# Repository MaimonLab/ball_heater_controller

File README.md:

# Ball Heater Controller

This repo contains the schematics and associated code for a controller to control the temperature of a ball holder or other device using closed loop PID drive of a resistive heater. There is a Python class to interact with the controller over USB-Serial, as well as a ROS2 Node to send and receive commands with the controller using ROS2.

For instructions on building a Ball Heater Controller, see [Assembly.](docs/assembly.md)

## Basic Usage

The Ball Heater Controller can be used independently of a computer by simply supplying it with AC power and attaching a ball heater and thermistor assembly to the main 4 pin output port on the front.

You can then change the mode by pressing and holding the control knob (see [Modes](#controller-modes)), and set the temperature setpoint (shown lower left as `SP:` on the LCD) by turning the knob. Current temperature is shown bottom right on the LCD.

### Python

The device can also be used with a computer for greater control and temperature logging. Interaction is done over USB-Serial, and the computer side is managed through the `BallHeaterDriver` Python class found in [`ball_heater_driver.py`](ball_heater_controller/ball_heater_controller/ball_heater_driver.py). An example of how this class can be used can be found in the Jupyter Notebook [`ball_heater_controller_testing.ipynb`](ball_heater_controller/ball_heater_controller/ball_heater_controller_testing.ipynb)

In short, after creating a `BallHeaterDriver` object, providing the correct serial port, commands can be sent using the `send_command` method. The main commands you will use are `status`, `set_target_temp`, and `set_control_mode`. Valid syntax for creating an object and sending these commands is shown below, with the first valid serial port chosen by default.

```python
import ball_heater_driver 
from list_ports import list_ports
import time

ports = [
    port
    for port in list_ports()
    if port["manufacturer"] is not None and "Silicon Labs" in port["manufacturer"]
]
port = ports[0]["port"]
print(f"Using Port: {port}")
ball_heater = ball_heater_driver.BallHeaterDriver(port=port)

# wait for the device to reset
time.sleep(5)

# Get and print status
success, status = ball_heater.send_command('status', [])
print('current status is:')
print('\n'.join((f"{key} : {value}") for key, value in status.items()))

# Set the target temperature to 35 (will also set control mode to remote)
ball_heater.send_command("set_target_temp", [35])

# Set the control mode back to standby
ball_heater.send_command("set_control_mode", ["standby"])
```

### ROS2

There is also a ROS2 Node provided for interacting with the Ball Heater Controller, [`ball_heater_node.py`](ball_heater_controller/ball_heater_controller/ball_heater_node.py).  The launch file [example_ball_heater.launch.py](ball_heater_controller/launch/example_ball_heater.launch.py), along with the config file [example_config.yaml](ball_heater_controller/config/example_config.yaml) will launch the node, as well as an example client node that can interact with the ball_heater_node.  It will also launch the ball_heater_gui that will subscribe to and print the heater status, and let the user set the temperature setpoint.  Once installed, set the `serial_port` or `device_serial_number` in `example_config.yaml` and launch the launch file using

```bash
ros2 launch ball_heater_controller example_ball_heater.launch.py 
```

Generally, the `BallHeaterNode` must be given a `serial_port` or a `device_serial_number` to specify the controller. Then, the status information will be published to the `ball_heater_status_topic` (default `ball_heater_controller/status_topic`), and the temperature can be set by another node by publishing to the `ball_heater_set_temp_topic` (default `ball_heater_controller/set_temp_topic`)

## Sub-directories

* `ball_heater_controller` -- ROS2 Package with a Node to interact with and control the heater, as well as `ball_heater_driver.py` which contains a Python class `BallHeaterDriver` to interact with the controller.
* `ball_heater_controller_interfaces` -- ROS2 Package with custom message types associated with the above package.
* `ball_heater_controller_firmware` -- Firmware for the microcontroller at the center of the PCB.
* `ball_heater_controller_pcb` -- Design files and gerbers for the printed circuit board for the Ball Heater Controller.
* `ball_heater_controller_case` -- Vector files for laser cuttting the case for the Ball Heater Controller.
* `docs` -- Additional documentation.

## Controller Modes

The controller has several different modes, shown upper left on the LCD display, and its behavior will be different depending on what mode it is in. The mode can be changed using the `set_control_mode` command through the interface, or by pressing and holding the control knob on the front of the device for >= 1 second.

* **Standby** On startup, the controller will be in standby mode, and the heater will not be driven, but the temperature will be shown on screen.
* **Local Control**  Pressing the control from standby mode will switch into `local control` mode, and the temperature setpoint can then be adjusted by turning the control knob.  This mode is useful for running the ball heater without a computer attached, or without needing to set the temp from the computer.
* **Remote Control** In this mode, the setpoint temperature is set from the computer using the `set_target_temp` command. Any `set_target_temp` commands received by the controller will automatically switch the controller into this mode.
* **Error Mode** There are also several error modes discussed below in [Safety Cutoffs](#safety-cutoffs--troubleshooting)

## Install

Run the installation script

```bash
./install_dependencies.sh
```

## Safety Cutoffs / Troubleshooting

The ball heater firmware has several different safety cutoffs built in that will trigger different errors and shut down the heater to prevent overheating. Once one of these error modes has been activated, the heater output will shut down, and the type of error will be displayed on the LCD. Pressing and holding the control knob down will reset the device into standby mode if the error state has been resolved.

1. **High temp error:** If the heater temperature sensor reads over 60 °C, the device will go into *High temp error* and shutdown.  
2. **No Temp Sensor:**  If the temperature sensor for the ball heater is not detected because it has been unpluged or a wire has broken, the device will go into *No Temp Sensor Error* and shutdown. When the sensor is replaced, the device will return to standby mode. Note that this is only for the integrated temp sensor in the ball heater, not the optional aux temp sensor.
3. **Heater Non Responsive:** If the control loop drives the  heater at a high power for too long, eg if the temperature is not responding properly, the device will go into *Heater Non Responsive* error and shutdown.

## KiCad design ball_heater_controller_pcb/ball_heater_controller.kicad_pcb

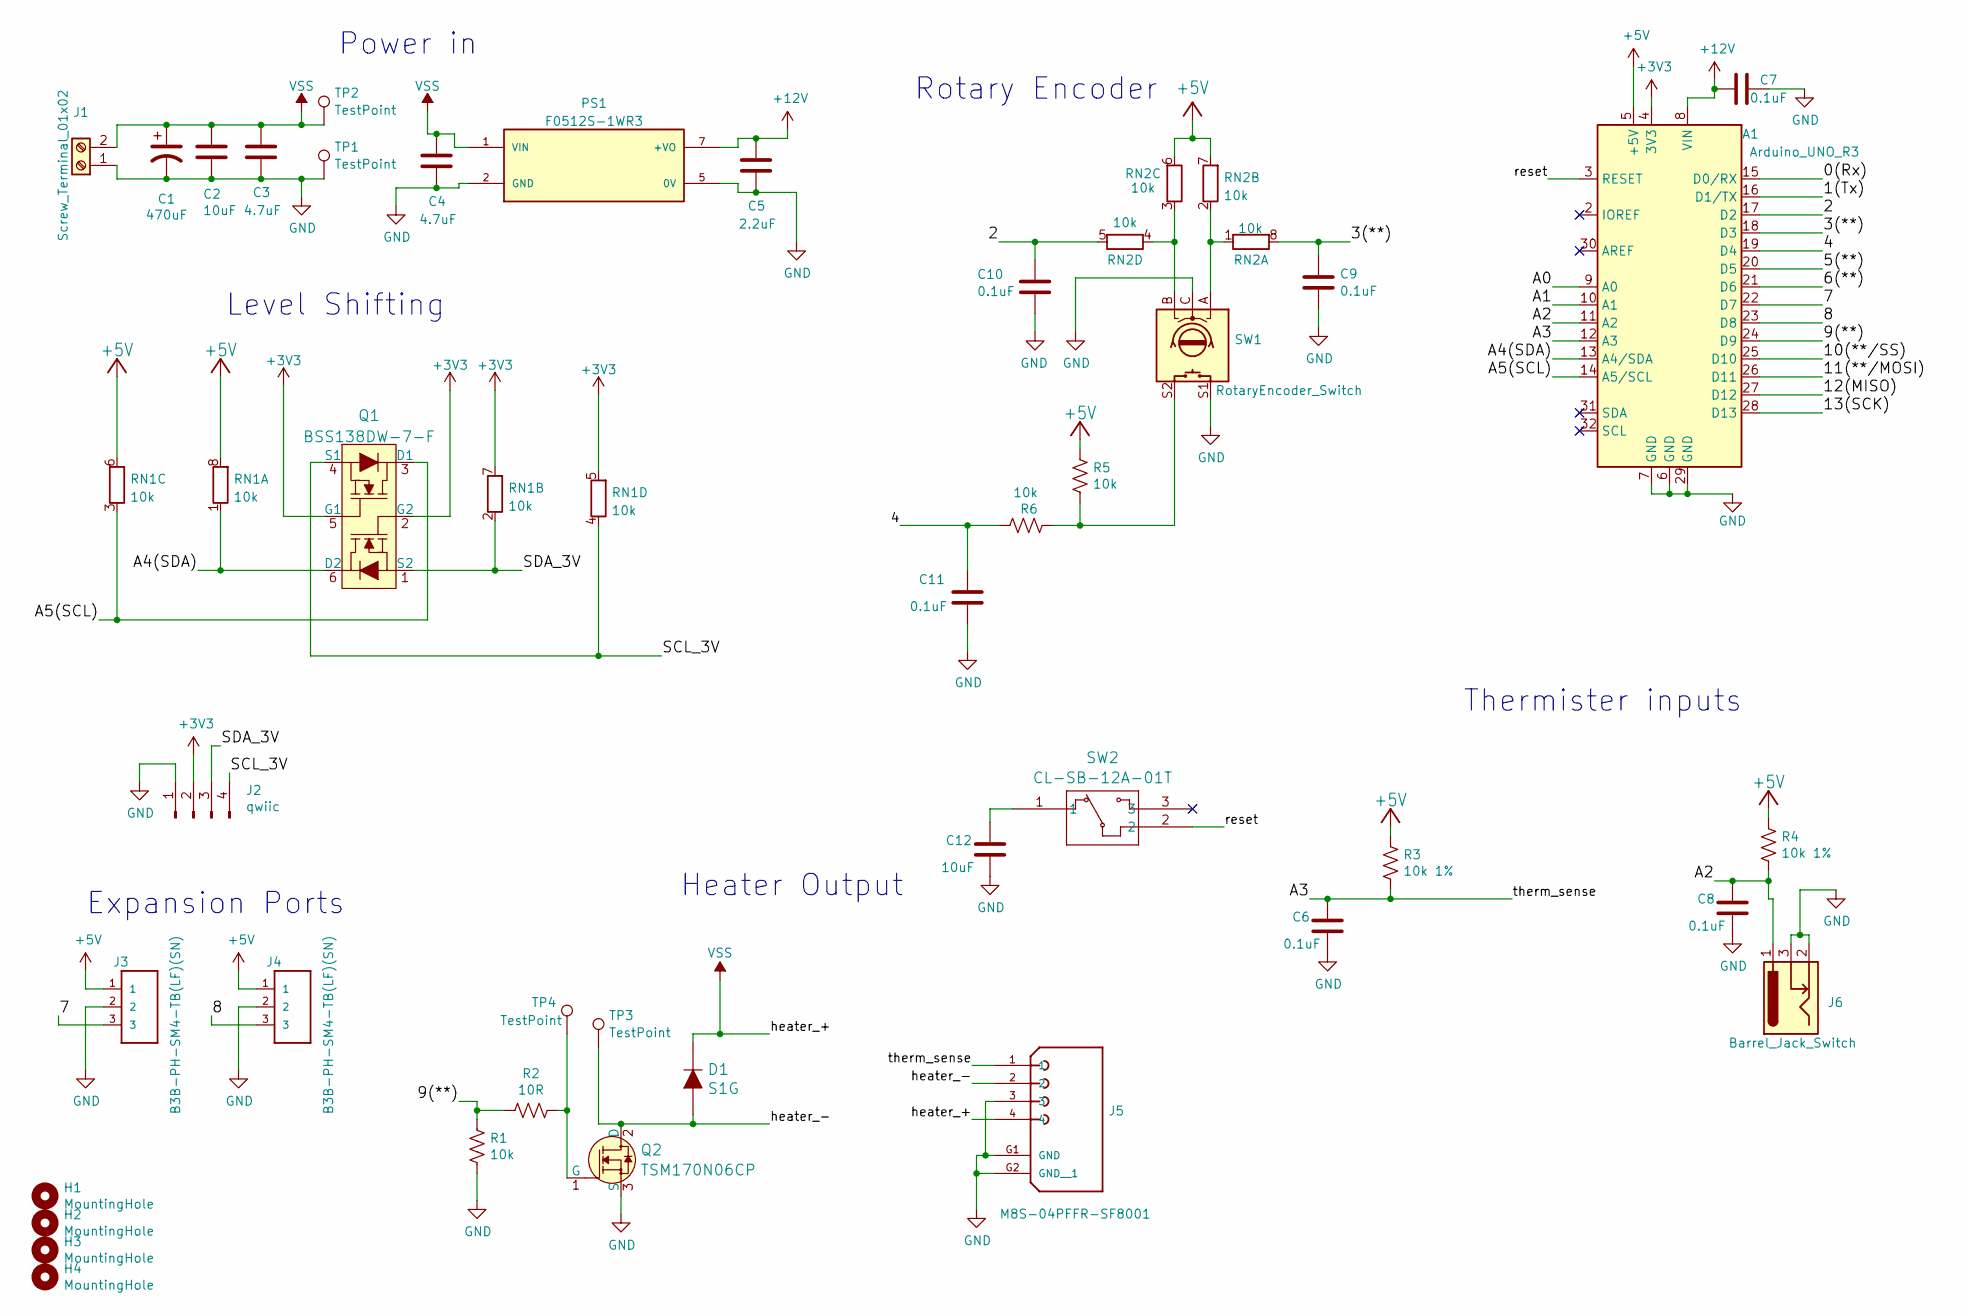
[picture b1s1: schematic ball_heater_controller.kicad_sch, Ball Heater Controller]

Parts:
A1: Arduino_UNO_R3; Metro_mini
C1: 470uF; CP_Radial_D12.5mm_P5.00mm
C2, C12: 10uF; C_0805_2012Metric_Pad1.18x1.45mm_HandSolder
C3, C4: 4.7uF; C_0805_2012Metric_Pad1.18x1.45mm_HandSolder
C5: 2.2uF; C_0805_2012Metric_Pad1.18x1.45mm_HandSolder
C6, C7, C8, C9, C10, C11: 0.1uF; C_0805_2012Metric_Pad1.18x1.45mm_HandSolder
D1: S1G; DO-214AC; MPN S1G; Digi-Key_PN S1GFSCT-ND
H1, H2, H3, H4: MountingHole; MountingHole_3.7mm
J1: Screw_Terminal_01x02; Term_Block_1x2_P5.08MM
J2: qwiic; BM04B-SRSS-TB(LF)(SN)
J3, J4: B3B-PH-SM4-TB(LF)(SN); JST_PH_B3B-PH-SM4-TB_1x03-1MP_P2.00mm_Vertical
J5: M8S-04PFFR-SF8001; AMPHENOL_M8S-04PFFR-SF8001; PARTREV B
J6: Barrel_Jack_Switch; BarrelJack_Horizontal
PS1: F0512S-1WR3; CONV_F0512S-1WR3; PARTREV 2021.12.28-A/6
Q1: BSS138DW-7-F; SOT-363; MPN BSS138DW-7-F; Digi-Key_PN BSS138DW-FDICT-ND
Q2: TSM170N06CP; TO-252-3; MPN TSM170N06CP; Digi-Key_PN TSM170N06CPROGCT-ND
R1, R5, R6: 10k; R_0805_2012Metric_Pad1.20x1.40mm_HandSolder
R2: 10R; R_0805_2012Metric_Pad1.20x1.40mm_HandSolder
R3, R4: 10k 1%; R_0805_2012Metric_Pad1.20x1.40mm_HandSolder
RN1, RN2: 10k; R_Array_Convex_4x1206
SW1: RotaryEncoder_Switch; RotaryEncoder_Bourns_Horizontal_PEC09-2xxxF-Sxxxx
SW2: CL-SB-12A-01T
TP1, TP2, TP3, TP4: TestPoint; TestPoint_Loop_D2.60mm_Drill1.6mm_Beaded

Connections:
+3V3: A1.4 (3V3), J2.2, Q1.2 (G2), Q1.5 (G1), RN1.5 (R4.2), RN1.7 (R2.2)
+5V: A1.5 (+5V), J3.1, J4.1, R3.1, R4.1, R5.1, RN1.6 (R3.2), RN1.8 (R1.2), RN2.6 (R3.2), RN2.7 (R2.2)
+12V: A1.8 (VIN), C5.1, C7.2, PS1.7 (+VO)
/0(Rx): A1.15 (D0/RX)
/1(Tx): A1.16 (D1/TX)
/2: A1.17 (D2), C10.1, RN2.5 (R4.2)
/3(**): A1.18 (D3), C9.1, RN2.8 (R1.2)
/4: A1.19 (D4), C11.1, R6.1
/5(**): A1.20 (D5)
/6(**): A1.21 (D6)
/7: A1.22 (D7), J3.3
/8: A1.23 (D8), J4.3
/9(**): A1.24 (D9), R1.2, R2.2
/10(**/SS): A1.25 (D10)
/11(**/MOSI): A1.26 (D11)
/12(MISO): A1.27 (D12)
/13(SCK): A1.28 (D13)
/A0: A1.9 (A0)
/A1: A1.10 (A1)
/A2: A1.11 (A2), C8.1, J6.1, R4.2
/A3: A1.12 (A3), C6.1, J5.1, R3.2
/A4(SDA): A1.13 (A4/SDA), Q1.6 (D2), RN1.1 (R1.1)
/A5(SCL): A1.14 (A5/SCL), Q1.3 (D1), RN1.3 (R3.1)
/SCL_3V: J2.4, Q1.4 (S1), RN1.4 (R4.1)
/SDA_3V: J2.3, Q1.1 (S2), RN1.2 (R2.1)
/heater_-: D1.A, J5.2, Q2.2 (D), TP3.1
/reset: A1.3 (RESET), SW2.2
GND: A1.6 (GND), A1.7 (GND), A1.29 (GND), C1.2, C2.2, C3.2, C4.2, C5.2, C6.2, C7.1, C8.2, C9.2, C10.2, C11.2, C12.2, J1.1, J2.1, J3.2, J4.2, J5.3, J5.G1 (GND), J5.G2 (GND__1), J6.2, J6.3, PS1.2 (GND), PS1.5 (0V), Q2.3 (S), R1.1, SW1.C, SW1.S1, TP1.1
unnamed: C12.1, SW2.1
unnamed: Q2.1 (G), R2.1, TP4.1
unnamed: R5.2, R6.2, SW1.S2
unnamed: RN2.1 (R1.1), RN2.2 (R2.1), SW1.A
unnamed: RN2.3 (R3.1), RN2.4 (R4.1), SW1.B
VSS: C1.1, C2.1, C3.1, C4.1, D1.K, J1.2, J5.4, PS1.1 (VIN), TP2.1

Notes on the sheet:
Power in
Heater Output
Thermister inputs
Expansion Ports
Rotary Encoder
Level Shifting

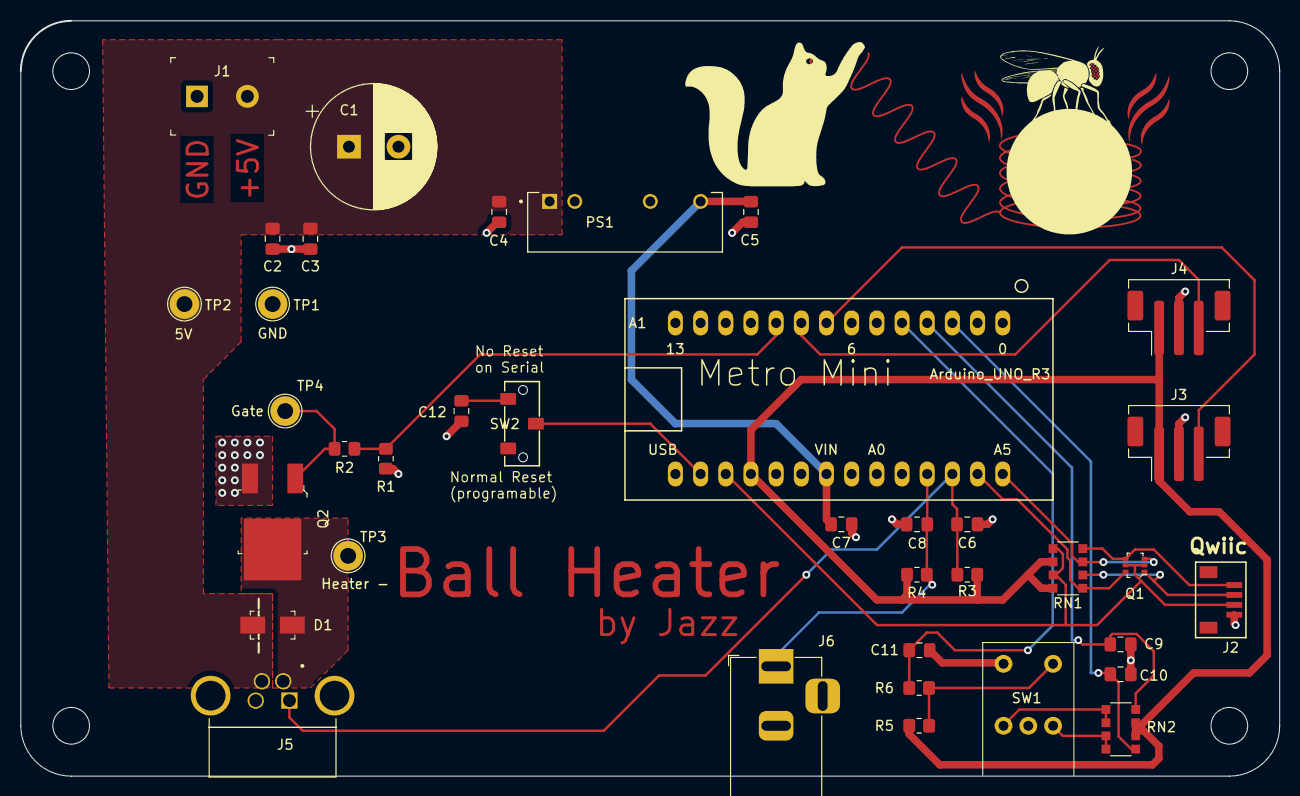
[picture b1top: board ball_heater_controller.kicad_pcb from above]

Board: 2 copper layers, 127.0 x 76.2 mm, 41 parts (0 on the bottom side), 24 nets.

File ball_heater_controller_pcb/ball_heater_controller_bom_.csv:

Component,Description,Part,References,Value,Footprint,Quantity Per PCB,Datasheet,Field4,Field5,Field6,Field7,Field8,MANUFACTURER,MAXIMUM_PACKAGE_HEIGHT,PARTREV,STANDARD,Category,DK_Datasheet_Link,DK_Detail_Page,Digi-Key_PN,Family,MPN,Manufacturer,Status
1,,Arduino_UNO_R3-MCU_Module,A1,Arduino_UNO_R3,Metro_mini,1,https://www.arduino.cc/en/Main/arduinoBoardUno,,,,,,,,,,,,,,,,,
2,Unpolarized capacitor,C,C6 C7 C8,0.1uF,C_0805_2012Metric_Pad1.18x1.45mm_HandSolder,3,~,,,,,,,,,,,,,,,,,
3,Unpolarized capacitor,C,C5,2.2uF,C_0805_2012Metric_Pad1.18x1.45mm_HandSolder,1,~,,,,,,,,,,,,,,,,,
4,Unpolarized capacitor,C,C3 C4,4.7uF,C_0805_2012Metric_Pad1.18x1.45mm_HandSolder,2,~,,,,,,,,,,,,,,,,,
5,Unpolarized capacitor,C,C2,10uF,C_0805_2012Metric_Pad1.18x1.45mm_HandSolder,1,~,,,,,,,,,,,,,,,,,
6,,CP1-Device,C1,470uF,CP_Radial_D12.5mm_P5.00mm,1,,,,,,,,,,,,,,,,,,
7,,D_ALT-Device,D1,BAS316,D_SOD-323_HandSoldering,1,,,,,,,,,,,,,,,,,,
8,,B3B-PH-SM4-TB(LF)(SN),J3 J4,B3B-PH-SM4-TB(LF)(SN),JST_PH_B3B-PH-SM4-TB_1x03-1MP_P2.00mm_Vertical,2,https://www.digikey.com/product-detail/en/jst-sales-america-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,B3B-PH-SM4-TB_LF__SN_,PH Series 3 Position 2 mm Pitch Crimp Surface Mount Top Entry Shrouded Header,2010 JST,JST Sales,455-1735-1-ND,,,,,,,,,,,,
9,DC Barrel Jack with an internal switch,Barrel_Jack_Switch,J6,Barrel_Jack_Switch,BarrelJack_Horizontal,1,~,,,,,,,,,,,,,,,,,
10,,M8S-04PFFR-SF8001,J5,M8S-04PFFR-SF8001,AMPHENOL_M8S-04PFFR-SF8001,1,,,,,,,Amphenol,12.581 mm,B,Manufacturer Recommendations,,,,,,,,
11,"Generic screw terminal, single row, 01x02, script generated (kicad-library-utils/schlib/autogen/connector/)",Screw_Terminal_01x02,J1,Screw_Terminal_01x02,Term_Block_1x2_P5.08MM,1,~,,,,,,,,,,,,,,,,,
12,"Generic connector, single row, 01x04, script generated (kicad-library-utils/schlib/autogen/connector/)",Conn_01x04_Male,J2,qwiic,BM04B-SRSS-TB(LF)(SN),1,~,,,,,,,,,,,,,,,,,
13,,F0512S-1WR3,PS1,F0512S-1WR3,CONV_F0512S-1WR3,1,,,,,,,Mornsun,10.16 mm,2021.12.28-A/6,Manufacturer Recommendations,,,,,,,,
14,"N-MOSFET transistor, gate/source/drain",Q_NMOS_GSD,Q2,AON7528,TRANS_AON7403,1,~,,,,,,,,,,,,,,,,,
15,MOSFET 2N-CH 50V 0.2A SC70-6,BSS138DW-7-F,Q1,BSS138DW-7-F,SOT-363,1,https://www.diodes.com/assets/Datasheets/ds30203.pdf,,,,,,,,,,Discrete Semiconductor Products,https://www.diodes.com/assets/Datasheets/ds30203.pdf,/product-detail/en/diodes-incorporated/BSS138DW-7-F/BSS138DW-FDICT-ND/808541,BSS138DW-FDICT-ND,"Transistors - FETs, MOSFETs - Arrays",BSS138DW-7-F,Diodes Incorporated,Active
16,"Resistor, US symbol",R_US,R2,10R,R_0805_2012Metric_Pad1.20x1.40mm_HandSolder,1,~,,,,,,,,,,,,,,,,,
17,"Resistor, US symbol",R_US,R1,10k,R_0805_2012Metric_Pad1.20x1.40mm_HandSolder,1,~,,,,,,,,,,,,,,,,,
18,"Resistor, US symbol",R_US,R3 R4,10k 1%,R_0805_2012Metric_Pad1.20x1.40mm_HandSolder,2,~,,,,,,,,,,,,,,,,,
19,"4 resistor network, parallel topology, split",R_Pack04_Split,RN1,10k,R_Array_Convex_4x1206,1,~,,,,,,,,,,,,,,,,,
20,"Rotary encoder, dual channel, incremental quadrate outputs, with switch",RotaryEncoder_Switch,SW1,RotaryEncoder_Switch,PEC09-2320F-S0015,1,~,,,,,,,,,,,,,,,,,





Component Groups:,20
Component Count:,25
Fitted Components:,25
Number of PCBs:,1
Total components:,25
Schematic Version:,
Schematic Date:,
PCB Variant:,default
BoM Date:,"2023 October 12, Thursday 17:54:09"
Schematic Source:,ball_heater_controller.kicad_sch
KiCad Version:,Eeschema 7.0.8

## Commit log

2023-10-19 Initial Commit. PCB V1 ordered
2023-10-19 added readme
2023-10-20 adjusted PCB, added no-reset switch
2023-10-24 First version of firmware. PID and local control working
2023-10-24 added serial communication. working!
2023-10-24 Python class and test notebook working
2023-10-26 added logging to the python class and imporved test nb
2023-10-30 initial commit of ROS node etc for ball heater
2023-10-30 fixed directory structure. It builds now!
2023-10-30 fixed naming issues / inconsistencies
2023-10-30 fixed more naming and import issues
2023-10-30 fixed set temp function. it's alive!
2023-10-30 updated firmware. better errors and proper standby mode
2023-11-07 added control mode switching and fixed string bug
2023-11-07 added backlight changes to show mode
2023-11-10 added no temp sensor error fixed string parsing and backlight
2023-11-21 changed to porportional on measurement and updated some thingsn
2023-11-21 added 2 second watchdog timer
2023-11-22 added filter based non-responsive safety error.
2023-11-23 improved non responsive and other error handling
2023-11-26 updated readme and docs
2023-11-27 improved send_command and renamed and docs
2023-11-27 updated testing notebook as clear demo
2023-12-04 small updates and name changes
2023-12-04 added gui node to control and monitor the heater
2023-12-04 updated launch and bugfixes. ROS stuff works now!
2023-12-04 updated readme and install script
2023-12-05 added BOM and updated docs
2023-12-05 added enclosure files
2023-12-05 updated BOM
2023-12-08 updated assembly instructions and BOM
2023-12-08 updated assembly and added new enclosure
2023-12-14 updated BOM and printout
2023-12-21 updated assembly instructions
2024-01-25 Adjusted heater firmware settings. Programming first batch of controllers!
2024-01-26 added PCB pdf
2024-01-26 minor ROS Node updates
2024-01-26 fixed some bugs and naming inconsistencies
2024-01-30 fixed naming problems
2024-02-05 updated readme assembly instructions
2024-02-06 updated enclosure
2024-05-21 fixed wire length
2025-06-09 update to freesimplegui
2025-06-24 updated wire length / fuse size
